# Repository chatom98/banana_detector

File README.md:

# This project is WIP

# Overview
Device to detect Beta particles. Since only easy-to-come-by Beta emmiter I can get is a banana, let's call it a Banana detector.
The detector is based on many circuits available on the Internet with few tweaks.

# Function principle
Device utilizes set of PIN photo-diodes to detect passing Beta particles. 
Following analog circuit is only an I-V converter and amplifier with large amplification and little bit of filtering.
To reduce resistor noise I use T network inverting amplifier.

To detect voltage impulses caused by particle collisions STM32G031 is planned to be used.
Device might count caught particles over time and show such number on OLED I2C display as well as beeping with each collision.
Since I2C communication will add certain noise and since used MCU does not allow to split GND an GNDA, refresh rate of the display is planned low and measurement is conducted only in steady states.

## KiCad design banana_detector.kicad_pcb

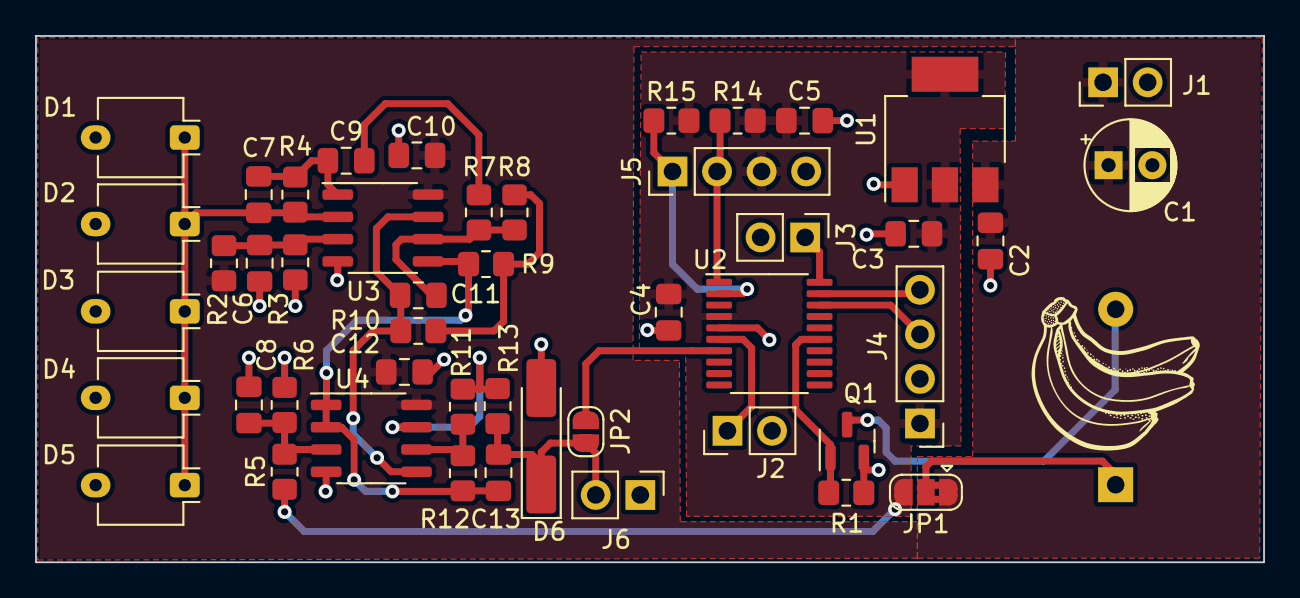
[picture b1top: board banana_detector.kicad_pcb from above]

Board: 2 copper layers, 70.0 x 30.0 mm, 48 parts (1 on the bottom side), 25 nets.

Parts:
C1: C_Polarized; CP_Radial_D5.0mm_P2.50mm
C2, C3, C5: 1u; C_0805_2012Metric_Pad1.18x1.45mm_HandSolder
C4, C6, C8, C10, C12: 100n; C_0805_2012Metric_Pad1.18x1.45mm_HandSolder
C7: 5p; C_0805_2012Metric_Pad1.18x1.45mm_HandSolder
C9: 470n; C_0805_2012Metric_Pad1.18x1.45mm_HandSolder
C11: 3n3; C_0805_2012Metric_Pad1.18x1.45mm_HandSolder
C13: 10n; C_0805_2012Metric_Pad1.18x1.45mm_HandSolder
D1, D2, D3, D4, D5: BPW34; Osram_DIL2_4.3x4.65mm_P5.08mm
D6: 3V3 zener; D_MiniMELF_Handsoldering
J1: supply; PinHeader_1x02_P2.54mm_Vertical
J2: NRST_button; PinHeader_1x02_P2.54mm_Vertical
J3: USER_button; PinHeader_1x02_P2.54mm_Vertical
J4, J5: Conn_01x04_Pin; PinHeader_1x04_P2.54mm_Vertical
J6: Conn_01x02_Pin; PinHeader_1x02_P2.54mm_Vertical
JP1: SolderJumper_3_Bridged12; SolderJumper-3_P1.3mm_Bridged2Bar12_RoundedPad1.0x1.5mm
JP2: Jumper_2_Open; SolderJumper-2_P1.3mm_Open_RoundedPad1.0x1.5mm
LS1: Speaker_Crystal; Buzzer_D14mm_H7mm_P10mm
Q1: BSS123; SOT-23
R1, R8, R10: 100k; R_0805_2012Metric_Pad1.20x1.40mm_HandSolder
R2: 1k; R_0805_2012Metric_Pad1.20x1.40mm_HandSolder
R3: 3k3; R_0805_2012Metric_Pad1.20x1.40mm_HandSolder
R4: 1Meg; R_0805_2012Metric_Pad1.20x1.40mm_HandSolder
R5, R6: 33k; R_0805_2012Metric_Pad1.20x1.40mm_HandSolder
R7, R9, R14, R15: 4k7; R_0805_2012Metric_Pad1.20x1.40mm_HandSolder
R11: 68k; R_0805_2012Metric_Pad1.20x1.40mm_HandSolder
R12: 6k8; R_0805_2012Metric_Pad1.20x1.40mm_HandSolder
R13: 470R; R_0805_2012Metric_Pad1.20x1.40mm_HandSolder
U1: AMS1117; SOT-223-3_TabPin2
U2: STM32G030F6Px; TSSOP-20_4.4x6.5mm_P0.65mm
U3, U4: TL082; SO-8_3.9x4.9mm_P1.27mm

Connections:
+3.3V: C3.1, C4.1, C5.1, J4.1, J5.3, JP1.3 (B), R5.1, R14.2, R15.2, U1.2 (VO), U2.4 (VDD)
+9V: C1.1, C2.1, C10.1, C12.1, J1.1, JP1.1 (A), R2.1, U1.3 (VI), U3.8 (V+), U4.8 (V+)
/I2C1_SCL: J5.2, R14.1, U2.1 (PB7/PB8)
/I2C1_SDA: J5.1, R15.1, U2.2 (PC14/PB9)
/SYS_SWCLK: J4.4, U2.19 (PA14/PA15)
/SYS_SWDIO: J4.3, U2.18 (PA13)
/adc_in: JP2.2 (B), U2.7 (PA0)
/analog/Vref: C13.2, R9.1, R12.1, U3.5 (+), U4.1, U4.2 (-)
/buzzer: Q1.1 (G), R1.1, U2.15 (PB0/PB1/PB2/PA8)
GND: C1.2, C2.2, C3.2, C4.2, C5.2, C6.2, C8.2, C10.2, C12.2, D1.2 (A), D2.2 (A), D3.2 (A), D4.2 (A), D5.2 (A), D6.2 (A), J1.2, J2.2, J3.2, J4.2, J5.4, J6.1, Q1.2 (S), R1.2, R3.1, R6.2, U1.1 (ADJ), U2.5 (VSS), U3.4 (V-), U4.4 (V-)
unnamed: C7.2, C9.1, R4.2, U3.1
unnamed: C9.2, R7.1
unnamed: C7.1, D1.1 (K), D2.1 (K), D3.1 (K), D4.1 (K), D5.1 (K), R4.1, U3.2 (-)
unnamed: C13.1, D6.1 (K), J6.2, JP2.1 (A), R13.2
unnamed: J2.1, U2.6 (NRST)
unnamed: J3.1, U2.20 (PB3/PB4/PB5/PB6)
unnamed: JP1.2 (C), LS1.1
unnamed: LS1.2, Q1.3 (D)
unnamed: R8.2, R9.2, R10.1
unnamed: R11.1, R13.1, U4.7
unnamed: C6.1, R2.2, R3.2, U3.3 (+)
unnamed: C11.1, R7.2, R8.1, U3.6 (-)
unnamed: C8.1, R5.2, R6.1, U4.3 (+)
unnamed: C11.2, R10.2, U3.7, U4.5 (+)
unnamed: R11.2, R12.2, U4.6 (-)

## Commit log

2024-05-29 ready for the firts trial
2024-05-29 added pcb image
2024-06-01 op amp type update, lm358->tl082, bulk purchase=cheaper, higher badwidth, still super cheap
